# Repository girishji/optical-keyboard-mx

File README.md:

# Baremetal Optical Keyboard Using Gateron MX Optical Switches

Optical keyboard PCB based on Gateron MX optical switches (KiCad project).

Keyboard matrix uses column-to-row scanning approach. The IR
(infra-red) led's in each column is connected to a GPIO pin configured as
output. A column is powered by setting the pin HIGH.
Each row is connected to a GPIO pin configured as input so that voltage drop
across the load register of PT (Phototransistor) can be read.

QMK code is in a [PR](https://github.com/qmk/qmk_firmware/pull/17852). In the
qmk tree you could find it in `keyboards/opticalkb/rev1` folder.

This is not a high-performance keyboard since IR's are provided with very
minimal current (way below the suggested operating value). This is done so as
to keep the design simple. A single GPIO pin of STM32F4 (set as output)
can provide 20 ma. Each IR is supplied with ~3.6 ma. The total current for 5
rows (IRs) falls within the allowable maximum current per pin. Yet it achieves
a scan rate of 400 hz. Since there is no debounce delay the latency (before USB
transit) is 2.5 ms. Compared to mechanical keyboards (with 5 ms debounce delay)
this keyboard achieves respectable performance. It is possible to push scanning
rate much higher, but it requires a different matrix design and additional switching
components to increase current to IR. 

Follow the [blog](https://girishji.github.io/) for more keyboard designs in the future.

### BUILD

It takes minimal effort to put together this keyboard. When you order from
jlcpcb have them assemble only 2 (out of 5) pcbs with SMD components (choose
green FR4). The other pcb's can be used as base plates. The two pcb's (one
with SMD assembly and one without) are soldered together using a special type
of tin-coated standoff. If you are using a heatgun use solder paste generously.
If using soldering iron solder from back of the standoff also.
Then screw the switch plate on top. There is
also a wrist rest. You can eliminate the wrist area completely by editing the
*Edge Cuts* layer of main pcb. All pcb's are 1.6 mm thickness.

All the part numbers (of jlcpcb) are embedded in the symbols so you can generate BOM.

Switch plate is in `switch-plate` folder. Wrist support is in `wrist-support` folder.

### PARTS

- SMTSO-M2-3.5ET standoff (17 pcs)
- M2x4mm screws (17 pcs)
- Blackpill STM32F401 MCU

For wrist support:

- M2x4mm screws (8 pcs)
- SMTSO-M2-10ET standoff (8)

### PICS

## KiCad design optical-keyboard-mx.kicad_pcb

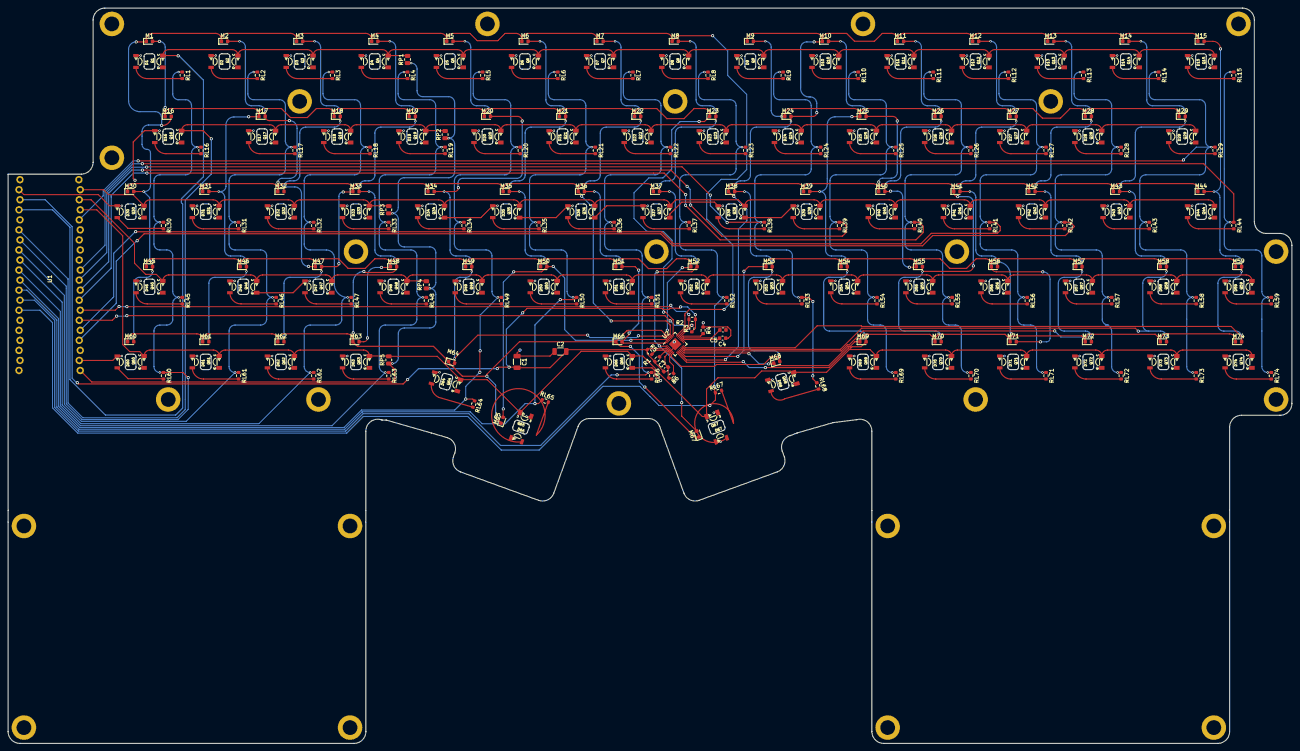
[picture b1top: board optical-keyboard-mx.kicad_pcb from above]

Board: 2 copper layers, 324.8 x 186.0 mm, 413 parts (0 on the bottom side), 122 nets.

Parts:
C1, C2: C_tant; C_1206_3216Metric
C3, C5: C_filt; C_0603_1608Metric
C4: C_aud_filt; C_0603_1608Metric
D1, D2, D3, D4, D5, D6, D7, D8, D9, D10, D11, D12, D13, D14, D15, D16, D17, D18, D19, D20, D21, D22, D23, D24, D25, D26, D27, D28, D29, D30, D31, D32, D33, D34, D35, D36, D37, D38, D39, D40, D41, D42, D43, D44, D45, D46, D47, D48, D49, D50, D51, D52, D53, D54, D55, D56, D57, D58, D59, D60, D61, D62, D63, D64, D65, D66, D67, D68, D69, D70, D71, D72, D73, D74: IR_LED; Everlight_IR_IR12-21C_TR8
H1, H2, H3, H4, H5, H6, H7, H8, H9, H10, H11, H12, H13, H14, H15, H16, H17: MountingHoleStdoffM2; SMTSO_M2
HS1, HS2, HS3, HS4, HS5, HS6, HS7, HS8: MountingHoleSprt; SMTSO_M2
M1, M2, M3, M4, M5, M6, M7, M8, M9, M10, M11, M12, M13, M14, M15, M16, M17, M18, M19, M20, M21, M22, M23, M24, M25, M26, M27, M28, M29, M30, M31, M32, M33, M34, M35, M36, M37, M38, M39, M40, M41, M42, M43, M44, M45, M46, M47, M48, M49, M50, M51, M52, M53, M54, M55, M56, M57, M58, M59, M60, M61, M62, M63, M64, M65, M66, M67, M68, M69, M70, M71, M72, M73, M74: LED; D_0603_1608Metric
Q1, Q2, Q3, Q4, Q5, Q6, Q7, Q8, Q9, Q10, Q11, Q12, Q13, Q14, Q15, Q16, Q17, Q18, Q19, Q20, Q21, Q22, Q23, Q24, Q25, Q26, Q27, Q28, Q29, Q30, Q31, Q32, Q33, Q34, Q35, Q36, Q37, Q38, Q39, Q40, Q41, Q42, Q43, Q44, Q45, Q46, Q47, Q48, Q49, Q50, Q51, Q52, Q53, Q54, Q55, Q56, Q57, Q58, Q59, Q60, Q61, Q62, Q63, Q64, Q65, Q66, Q67, Q68, Q69, Q70, Q71, Q72, Q73, Q74: Q_Photo_NPN; Everlight_PT_PT12-21C_TR8
R1, R2, R3, R4, R5, R6: R_a; R_0603_1608Metric
RL1, RL2, RL3, RL4, RL5, RL6, RL7, RL8, RL9, RL10, RL11, RL12, RL13, RL14, RL15, RL16, RL17, RL18, RL19, RL20, RL21, RL22, RL23, RL24, RL25, RL26, RL27, RL28, RL29, RL30, RL31, RL32, RL33, RL34, RL35, RL36, RL37, RL38, RL39, RL40, RL41, RL42, RL43, RL44, RL45, RL46, RL47, RL48, RL49, RL50, RL51, RL52, RL53, RL54, RL55, RL56, RL57, RL58, RL59, RL60, RL61, RL62, RL63, RL64, RL65, RL66, RL67, RL68, RL69, RL70, RL71, RL72, RL73, RL74: 560R; R_0603_1608Metric
RP1, RP2, RP3, RP4, RP5: 6.8k; R_0805_2012Metric
S1, S2, S3, S4, S5, S6, S7, S8, S9, S10, S11, S12, S13, S14, S15, S16, S17, S18, S19, S20, S21, S22, S23, S24, S25, S26, S27, S28, S29, S30, S31, S32, S33, S34, S35, S36, S37, S38, S39, S40, S41, S42, S43, S44, S45, S46, S47, S48, S49, S50, S51, S52, S53, S54, S55, S56, S57, S58, S59, S60, S61, S62, S63, S64, S65, S66, S67, S68, S69, S70, S71, S72, S73, S74: Gateron_Optical; Gateron_Sw_1u
U1: BlackPill_STLINK; BlackPill_STLINK_Down
U2: IS31FL3731-QF; QFN-28-1EP_4x4mm_P0.4mm_EP2.3x2.3mm

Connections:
+3.3V: RP1.1, RP2.1, RP3.1, RP4.1, RP5.1, U1.20 (3V3)
/col1: RL1.1, RL16.1, RL30.1, RL45.1, RL60.1, U1.34 (PB0)
/col2: RL2.1, RL17.1, RL31.1, RL46.1, RL61.1, U1.33 (PA7)
/col3: RL3.1, RL18.1, RL32.1, RL47.1, RL62.1, U1.32 (PA6)
/col4: RL4.1, RL19.1, RL33.1, RL48.1, RL63.1, U1.31 (PA5)
/col5: RL5.1, RL20.1, RL34.1, RL49.1, RL64.1, U1.30 (PA4)
/col6: RL6.1, RL21.1, RL35.1, RL50.1, RL65.1, U1.29 (PA3)
/col7: RL7.1, RL22.1, RL36.1, RL51.1, RL66.1, U1.28 (PA2)
/col8: RL8.1, RL23.1, RL37.1, RL52.1, RL67.1, U1.27 (PA1)
/col9: RL9.1, RL24.1, RL38.1, RL53.1, RL68.1, U1.11 (PB3)
/col10: RL10.1, RL25.1, RL39.1, RL54.1, RL69.1, U1.12 (PB4)
/col11: RL11.1, RL26.1, RL40.1, RL55.1, RL70.1, U1.13 (PB5)
/col12: RL12.1, RL27.1, RL41.1, RL56.1, RL71.1, U1.16 (PB8)
/col13: RL13.1, RL28.1, RL42.1, RL57.1, RL72.1, U1.17 (PB9)
/col14: RL14.1, RL29.1, RL43.1, RL58.1, RL73.1, U1.5 (PA8)
/col15: RL15.1, RL44.1, RL59.1, RL74.1, U1.10 (PA15)
/row1: Q1.1 (C), Q2.1 (C), Q3.1 (C), Q4.1 (C), Q5.1 (C), Q6.1 (C), Q7.1 (C), Q8.1 (C), Q9.1 (C), Q10.1 (C), Q11.1 (C), Q12.1 (C), Q13.1 (C), Q14.1 (C), Q15.1 (C), RP1.2, U1.37 (PB10)
/row2: Q16.1 (C), Q17.1 (C), Q18.1 (C), Q19.1 (C), Q20.1 (C), Q21.1 (C), Q22.1 (C), Q23.1 (C), Q24.1 (C), Q25.1 (C), Q26.1 (C), Q27.1 (C), Q28.1 (C), Q29.1 (C), RP2.2, U1.35 (PB1)
/row3: Q30.1 (C), Q31.1 (C), Q32.1 (C), Q33.1 (C), Q34.1 (C), Q35.1 (C), Q36.1 (C), Q37.1 (C), Q38.1 (C), Q39.1 (C), Q40.1 (C), Q41.1 (C), Q42.1 (C), Q43.1 (C), Q44.1 (C), RP3.2, U1.2 (PB13)
/row4: Q45.1 (C), Q46.1 (C), Q47.1 (C), Q48.1 (C), Q49.1 (C), Q50.1 (C), Q51.1 (C), Q52.1 (C), Q53.1 (C), Q54.1 (C), Q55.1 (C), Q56.1 (C), Q57.1 (C), Q58.1 (C), Q59.1 (C), RP4.2, U1.3 (PB14)
/row5: Q60.1 (C), Q61.1 (C), Q62.1 (C), Q63.1 (C), Q64.1 (C), Q65.1 (C), Q66.1 (C), Q67.1 (C), Q68.1 (C), Q69.1 (C), Q70.1 (C), Q71.1 (C), Q72.1 (C), Q73.1 (C), Q74.1 (C), RP5.2, U1.4 (PB15)
CA1: M1.1 (K), M2.1 (K), M3.1 (K), M4.1 (K), M5.1 (K), M6.1 (K), M7.1 (K), M8.1 (K), M16.2 (A), M30.2 (A), M45.2 (A), M60.2 (A), U2.21 (CA1)
CA2: M1.2 (A), M16.1 (K), M17.1 (K), M18.1 (K), M19.1 (K), M20.1 (K), M21.1 (K), M22.1 (K), M23.1 (K), M31.2 (A), M46.2 (A), M61.2 (A), U2.22 (CA2)
CA3: M2.2 (A), M17.2 (A), M30.1 (K), M31.1 (K), M32.1 (K), M33.1 (K), M34.1 (K), M35.1 (K), M36.1 (K), M37.1 (K), M47.2 (A), M62.2 (A), U2.23 (CA3)
CA4: M3.2 (A), M18.2 (A), M32.2 (A), M45.1 (K), M46.1 (K), M47.1 (K), M48.1 (K), M49.1 (K), M50.1 (K), M51.1 (K), M52.1 (K), M63.2 (A), U2.24 (CA4)
CA5: M4.2 (A), M19.2 (A), M33.2 (A), M48.2 (A), M60.1 (K), M61.1 (K), M62.1 (K), M63.1 (K), M64.1 (K), M65.1 (K), M66.1 (K), M67.1 (K), U2.25 (CA5)
CA6: M5.2 (A), M20.2 (A), M34.2 (A), M49.2 (A), M64.2 (A), U2.26 (CA6)
CA7: M6.2 (A), M21.2 (A), M35.2 (A), M50.2 (A), M65.2 (A), U2.27 (CA7)
CA8: M7.2 (A), M22.2 (A), M36.2 (A), M51.2 (A), M66.2 (A), U2.28 (CA8)
CA9: M8.2 (A), M23.2 (A), M37.2 (A), M52.2 (A), M67.2 (A), U2.1 (CA9)
CB1: M9.1 (K), M10.1 (K), M11.1 (K), M12.1 (K), M13.1 (K), M14.1 (K), M15.1 (K), M24.2 (A), M38.2 (A), M53.2 (A), M68.2 (A), U2.7 (CB1)
CB2: M9.2 (A), M24.1 (K), M25.1 (K), M26.1 (K), M27.1 (K), M28.1 (K), M29.1 (K), M39.2 (A), M54.2 (A), M69.2 (A), U2.8 (CB2)
CB3: M10.2 (A), M25.2 (A), M38.1 (K), M39.1 (K), M40.1 (K), M41.1 (K), M42.1 (K), M43.1 (K), M44.1 (K), M55.2 (A), M70.2 (A), U2.9 (CB3)
CB4: M11.2 (A), M26.2 (A), M40.2 (A), M53.1 (K), M54.1 (K), M55.1 (K), M56.1 (K), M57.1 (K), M58.1 (K), M59.1 (K), M71.2 (A), U2.10 (CB4)
CB5: M12.2 (A), M27.2 (A), M41.2 (A), M56.2 (A), M68.1 (K), M69.1 (K), M70.1 (K), M71.1 (K), M72.1 (K), M73.1 (K), M74.1 (K), U2.11 (CB5)
CB6: M13.2 (A), M28.2 (A), M42.2 (A), M57.2 (A), M72.2 (A), U2.12 (CB6)
CB7: M14.2 (A), M29.2 (A), M43.2 (A), M58.2 (A), M73.2 (A), U2.13 (CB7)
CB8: M15.2 (A), M44.2 (A), M59.2 (A), M74.2 (A), U2.14 (CB8)
GND: C1.1, C2.1, C3.1, C5.1, D1.1 (K), D2.1 (K), D3.1 (K), D4.1 (K), D5.1 (K), D6.1 (K), D7.1 (K), D8.1 (K), D9.1 (K), D10.1 (K), D11.1 (K), D12.1 (K), D13.1 (K), D14.1 (K), D15.1 (K), D16.1 (K), D17.1 (K), D18.1 (K), D19.1 (K), D20.1 (K), D21.1 (K), D22.1 (K), D23.1 (K), D24.1 (K), D25.1 (K), D26.1 (K), D27.1 (K), D28.1 (K), D29.1 (K), D30.1 (K), D31.1 (K), D32.1 (K), D33.1 (K), D34.1 (K), D35.1 (K), D36.1 (K), D37.1 (K), D38.1 (K), D39.1 (K), D40.1 (K), D41.1 (K), D42.1 (K), D43.1 (K), D44.1 (K), D45.1 (K), D46.1 (K), D47.1 (K), D48.1 (K), D49.1 (K), D50.1 (K), D51.1 (K), D52.1 (K), D53.1 (K), D54.1 (K), D55.1 (K), D56.1 (K), D57.1 (K), D58.1 (K), D59.1 (K), D60.1 (K), D61.1 (K), D62.1 (K), D63.1 (K), D64.1 (K), D65.1 (K), D66.1 (K), D67.1 (K), D68.1 (K), D69.1 (K), D70.1 (K), D71.1 (K), D72.1 (K), D73.1 (K), D74.1 (K), Q1.2 (E), Q2.2 (E), Q3.2 (E), Q4.2 (E), Q5.2 (E), Q6.2 (E), Q7.2 (E), Q8.2 (E), Q9.2 (E), Q10.2 (E), Q11.2 (E), Q12.2 (E), Q13.2 (E), Q14.2 (E), Q15.2 (E), Q16.2 (E), Q17.2 (E), Q18.2 (E), Q19.2 (E), Q20.2 (E), Q21.2 (E), Q22.2 (E), Q23.2 (E), Q24.2 (E), Q25.2 (E), Q26.2 (E), Q27.2 (E), Q28.2 (E), Q29.2 (E), Q30.2 (E), Q31.2 (E), Q32.2 (E), Q33.2 (E), Q34.2 (E), Q35.2 (E), Q36.2 (E), Q37.2 (E), Q38.2 (E), Q39.2 (E), Q40.2 (E), Q41.2 (E), Q42.2 (E), Q43.2 (E), Q44.2 (E), Q45.2 (E), Q46.2 (E), Q47.2 (E), Q48.2 (E), Q49.2 (E), Q50.2 (E), Q51.2 (E), Q52.2 (E), Q53.2 (E), Q54.2 (E), Q55.2 (E), Q56.2 (E), Q57.2 (E), Q58.2 (E), Q59.2 (E), Q60.2 (E), Q61.2 (E), Q62.2 (E), Q63.2 (E), Q64.2 (E), Q65.2 (E), Q66.2 (E), Q67.2 (E), Q68.2 (E), Q69.2 (E), Q70.2 (E), Q71.2 (E), Q72.2 (E), Q73.2 (E), Q74.2 (E), R4.1, R6.2, U1.19 (GND), U1.39 (GND), U2.5 (GND), U2.29 (GND)
unnamed: C4.2, U2.17 (IN)
unnamed: C5.2, U2.16 (C_FILT)
unnamed: D1.2 (A), RL1.2
unnamed: D2.2 (A), RL2.2
unnamed: D3.2 (A), RL3.2
unnamed: D4.2 (A), RL4.2
unnamed: D5.2 (A), RL5.2
unnamed: D6.2 (A), RL6.2
unnamed: D7.2 (A), RL7.2
unnamed: D8.2 (A), RL8.2
unnamed: D9.2 (A), RL9.2
unnamed: D10.2 (A), RL10.2
unnamed: D11.2 (A), RL11.2
unnamed: D12.2 (A), RL12.2
unnamed: D13.2 (A), RL13.2
unnamed: D14.2 (A), RL14.2
unnamed: D15.2 (A), RL15.2
unnamed: D16.2 (A), RL16.2
unnamed: D17.2 (A), RL17.2
unnamed: D18.2 (A), RL18.2
unnamed: D19.2 (A), RL19.2
unnamed: D20.2 (A), RL20.2
unnamed: D21.2 (A), RL21.2
unnamed: D22.2 (A), RL22.2
unnamed: D23.2 (A), RL23.2
unnamed: D24.2 (A), RL24.2
unnamed: D25.2 (A), RL25.2
unnamed: D26.2 (A), RL26.2
unnamed: D27.2 (A), RL27.2
unnamed: D28.2 (A), RL28.2
unnamed: D29.2 (A), RL29.2
unnamed: D30.2 (A), RL30.2
unnamed: D31.2 (A), RL31.2
unnamed: D32.2 (A), RL32.2
unnamed: D33.2 (A), RL33.2
unnamed: D34.2 (A), RL34.2
unnamed: D35.2 (A), RL35.2
unnamed: D36.2 (A), RL36.2
unnamed: D37.2 (A), RL37.2
unnamed: D38.2 (A), RL38.2
unnamed: D39.2 (A), RL39.2
unnamed: D40.2 (A), RL40.2
unnamed: D41.2 (A), RL41.2
unnamed: D42.2 (A), RL42.2
unnamed: D43.2 (A), RL43.2
unnamed: D44.2 (A), RL44.2
unnamed: D45.2 (A), RL45.2
unnamed: D46.2 (A), RL46.2
unnamed: D47.2 (A), RL47.2
unnamed: D48.2 (A), RL48.2
unnamed: D49.2 (A), RL49.2
unnamed: D50.2 (A), RL50.2
unnamed: D51.2 (A), RL51.2
unnamed: D52.2 (A), RL52.2
unnamed: D53.2 (A), RL53.2
unnamed: D54.2 (A), RL54.2
unnamed: D55.2 (A), RL55.2
unnamed: D56.2 (A), RL56.2
unnamed: D57.2 (A), RL57.2
unnamed: D58.2 (A), RL58.2
unnamed: D59.2 (A), RL59.2
unnamed: D60.2 (A), RL60.2
unnamed: D61.2 (A), RL61.2
unnamed: D62.2 (A), RL62.2
unnamed: D63.2 (A), RL63.2
unnamed: D64.2 (A), RL64.2
unnamed: D65.2 (A), RL65.2
unnamed: D66.2 (A), RL66.2
unnamed: D67.2 (A), RL67.2
unnamed: D68.2 (A), RL68.2
unnamed: D69.2 (A), RL69.2
unnamed: D70.2 (A), RL70.2
unnamed: D71.2 (A), RL71.2
unnamed: D72.2 (A), RL72.2
unnamed: D73.2 (A), RL73.2
unnamed: D74.2 (A), RL74.2
unnamed: R1.2, U2.4 (~INTB)
unnamed: R4.2, U2.18 (AD)
unnamed: R5.2, U2.3 (~SDB)
unnamed: R6.1, U2.6 (R_EXT)
SCL: R2.2, U1.14 (PB6), U2.20 (SCL)
SDA: R3.2, U1.15 (PB7), U2.19 (SDA)
VCC: C1.2, C2.2, C3.2, R1.1, R2.1, R3.1, R5.1, U1.38 (3V3), U2.2 (VCC)

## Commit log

2022-08-09 M .gitignore A MyFootprints.pretty/AdafruitCharliplex2.kicad_mod A MyFootprints.pretty/BlackPill_STLINK.kicad_mod A MyFootprints.pretty/BlackPill_STLINK2.kicad_mod A MyFootprints.pretty/BlackPill_STL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
2022-08-11 Added traces through python script
    D MyFootprints.pretty/Gateron_Sw_1.25u.kicad_mod
    D MyFootprints.pretty/Gateron_Sw_1.5u.kicad_mod
    D MyFootprints.pretty/Gateron_Sw_1.75u.kicad_mod
    M MyFootprints.pretty/Gateron_Sw_1u.kicad_mod
    D MyFootprints.pretty/Gateron_Switch_Basic.kicad_mod
    M optical-keyboard-mx.kicad_pcb
2022-08-11 Python scripts to add curved tracks
    Script to place mouting holes, draw edge cuts.
    A MyFootprints.pretty/SMTSO_M1.6.kicad_mod
    A MyFootprints.pretty/SMTSO_M2.kicad_mod
    A drawborder.py
    M optical-keyboard-mx.kicad_pcb
    M optical-keyboard-mx.kicad_prl
2022-08-13 Add python script to draw edge cuts
    M MyFootprints.pretty/BlackPill_STLINK_Down.kicad_mod
    A MyFootprints.pretty/MountingHole_1.7mm_M1.6_Pad.kicad_mod
    A MyFootprints.pretty/MountingHole_2.2mm_M2_ISO7380_Pad.kicad_mod
    A MyFootprints.pretty/PinHeader_1x04_P2.54mm_Vertical.kicad_mod
    A MyFootprints.pretty/PinHeader_1x08_P2.54mm_Vertical.kicad_mod
    M MySymbols.kicad_sym
2022-08-13 rename file
    R placemx.py -> placefpg.mx
2022-08-13 rename file
    D placefpg.mx
    A placefpg.py
2022-08-13 rename file
    R placefpg.py -> placefp.py
    D placefpg.mx
2022-08-13 More scripts to draw border and place footprint
    M drawborder.py
    M mounting-hw.kicad_sch
    M optical-keyboard-mx.kicad_pcb
    M optical-keyboard-mx.kicad_sch
    M placefp.py
    D placefpg.mx
2022-08-15 Tracks laid, wrist support and switch plate
    M MyFootprints.pretty/BlackPill_STLINK_Down.kicad_mod
    M MyFootprints.pretty/SMTSO_M1.6.kicad_mod
    M MyFootprints.pretty/SMTSO_M2.kicad_mod
    M MyFootprints.pretty/Switch_Cutout.kicad_mod
    D MyFootprints.pretty/Switch_Cutout_1.25u.kicad_mod
    D MyFootprints.pretty/Switch_Cutout_1.5u.kicad_mod
2022-08-15 update deletion of file
    D placefpg.mx
2022-08-17 Add gerbers and assembly files
    M .gitignore
    M MyFootprints.pretty/MountingHole_2.2mm_M2_ISO7380_Pad.kicad_mod
    M MySymbols.kicad_sym
    M README.md
    M drawborder.py
    A jlcpcb/gerber/optical-keyboard-mx-B_Cu.gbl
2022-08-18 Reverse polarities of capacitor
    M jlcpcb/gerber/optical-keyboard-mx-B_Cu.gbl
    M jlcpcb/gerber/optical-keyboard-mx-B_Mask.gbs
    M jlcpcb/gerber/optical-keyboard-mx-B_Paste.gbp
    M jlcpcb/gerber/optical-keyboard-mx-B_Silkscreen.gbo
    M jlcpcb/gerber/optical-keyboard-mx-Edge_Cuts.gm1
    M jlcpcb/gerber/optical-keyboard-mx-F_Cu.gtl
2022-09-17 updated part numbers for jlcpcb
    M MySymbols.kicad_sym
    M drawborder.py
    M optical-keyboard-mx.kicad_sch
    M switch.kicad_sch
2022-09-17 update readme
    M README.md
2022-09-17 updated readme
    M README.md
2022-09-18 update
    M README.md
2022-10-15 Fix bug where SCL SDA of I2c not connected
    M drawborder.py
    M led_driver.kicad_sch
    M optical-keyboard-mx.kicad_pcb
    M optical-keyboard-mx.kicad_prl
    M optical-keyboard-mx.kicad_sch
